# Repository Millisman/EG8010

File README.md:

# EG8010
Collection of designs for the EG8010 (ASIC for single-phase SPWM control H-bridge)

# EG8010_A0
EG8010_A0 is the inverter version to replace EGS002. Uses TLP250 optical isolated drivers and a Totem-pole current amplifier to drive high gate capacitance MOSFET transistors. A four-pin Kelvin circuit is used for all connections.

The connection diagram has a minimum of parts. An external +5V power supply is not required if the 7805 is populated on board. The fan is controlled directly from the printed circuit board. Twisted wires are indicated by ovals. Please don't separate them.

# MIT License
Design is distributed under the terms of the MIT license.

You can use this project for personal and business.
You can make it and sell it.
You may modify this project as you see fit.
You are bound by the copyright.

NO WARRANTIES of any kind are given!

All actions are at your OWN RISK!

Copyright (c) 2023, Sergey Kostyanoy <contact@arduino.uno>

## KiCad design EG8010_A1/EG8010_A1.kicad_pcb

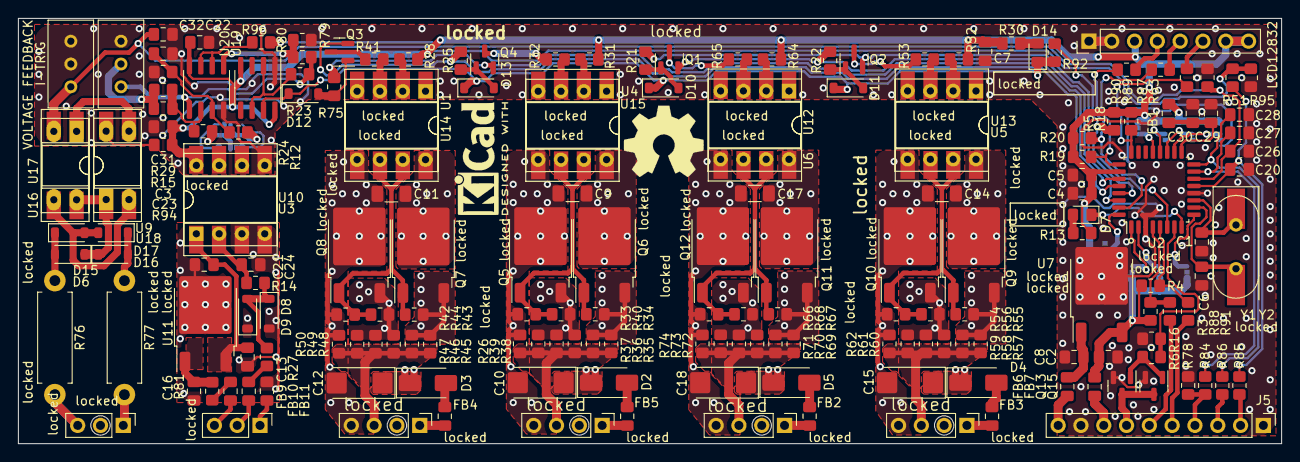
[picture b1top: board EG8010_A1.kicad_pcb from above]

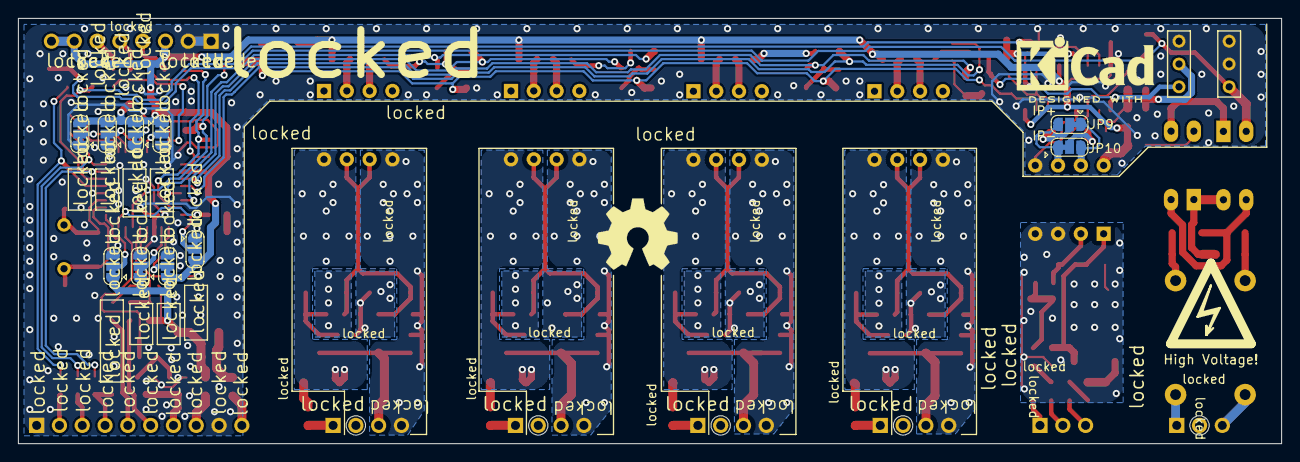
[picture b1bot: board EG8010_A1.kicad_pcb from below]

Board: 2 copper layers, 140.7 x 47.4 mm, 201 parts (13 on the bottom side), 123 nets.

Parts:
C1, C3, C6, C31: 22pF; C_0805_2012Metric_Pad1.18x1.45mm_HandSolder
C2, C4, C13, C16, C30, C32: 1uF; C_0805_2012Metric_Pad1.18x1.45mm_HandSolder
C5, C7, C8, C20, C21, C22, C23, C26, C27, C28, C29: 100nF; C_0805_2012Metric_Pad1.18x1.45mm_HandSolder
C9, C11, C14, C17: 10uF 50V; C_1206_3216Metric_Pad1.33x1.80mm_HandSolder
C10, C12, C15, C18: 10uF 35V; CP_EIA-6032-15_Kemet-U_Pad2.25x2.35mm_HandSolder
C24: 330pF; C_0805_2012Metric_Pad1.18x1.45mm_HandSolder
D2, D3, D4, D5: US1M; D_SMA
D6, D8, D9, D10, D11, D12, D13, D15, D16, D17: 1N4148W; D_SOD-123
D7: STATUS; LED_0805_2012Metric_Pad1.15x1.40mm_HandSolder
D14: OVC; LED_0805_2012Metric_Pad1.15x1.40mm_HandSolder
FB1, FB2, FB3, FB4, FB5, FB6, FB7, FB9, FB10, FB11: 600Ω@100MHz; C_0805_2012Metric_Pad1.18x1.45mm_HandSolder
HV1: High Voltage!; High_Voltage_Logo_10mm
J1, J2, J3, J4: C2.54_01x04_Pin; PinHeader_1x04_P2.54mm_Vertical
J5: Conn_01x10_Pin; PinHeader_1x10_P2.54mm_Vertical
J6: VOLTAGE; PinHeader_1x03_P2.54mm_Vertical
J7: CURRENT; PinHeader_1x03_P2.54mm_Vertical
JP1: FRQSEL1; SolderJumper-3_P1.3mm_Bridged12_RoundedPad1.0x1.5mm
JP2: FRQSEL0; SolderJumper-3_P1.3mm_Bridged12_RoundedPad1.0x1.5mm
JP3: DT0; SolderJumper-3_P1.3mm_Bridged12_RoundedPad1.0x1.5mm
JP4: DT1; SolderJumper-3_P1.3mm_Bridged12_RoundedPad1.0x1.5mm
JP5: VVVF; SolderJumper-3_P1.3mm_Bridged12_RoundedPad1.0x1.5mm
JP6: SST; SolderJumper-3_P1.3mm_Bridged12_RoundedPad1.0x1.5mm
JP7: MODSEL; SolderJumper-3_P1.3mm_Bridged12_RoundedPad1.0x1.5mm
JP8: SPWTYP; SolderJumper-3_P1.3mm_Bridged12_RoundedPad1.0x1.5mm
JP9: IP+; SolderJumper-3_P1.3mm_Bridged12_RoundedPad1.0x1.5mm
JP10: IP-; SolderJumper-3_P1.3mm_Bridged12_RoundedPad1.0x1.5mm
KICAD1: KiCad-Logo2_6mm_SilkScreen
KICAD2: KiCad-Logo2_5mm_SilkScreen
LCD12832: C2.54_01x08_Pin; PinHeader_1x08_P2.54mm_Vertical
OSHW1, OSHW2: Logo_Open_Hardware_Small; OSHW-Symbol_8.9x8mm_SilkScreen
Q1, Q2, Q3, Q4, Q13, Q15: 2N7002; SOT-23
Q5, Q8, Q10, Q12: PNP; TO-252-2
Q6, Q7, Q9, Q11: NPN; TO-252-2
R3, R4, R5, R12, R15, R16, R18, R19, R20, R24, R26, R29, R33, R42, R50, R51, R54, R62, R63, R66, R74, R78, R80, R84, R85, R86: 10K; R_0805_2012Metric_Pad1.20x1.40mm_HandSolder
R6, R13, R21, R22, R23, R25, R30, R75: 2.2K; R_0805_2012Metric_Pad1.20x1.40mm_HandSolder
R14, R27, R35, R36, R37, R38, R39, R45, R46, R47, R48, R49, R57, R58, R59, R60, R61, R69, R70, R71, R72, R73, R81: 4.7; R_0805_2012Metric_Pad1.20x1.40mm_HandSolder
R28, R31, R32, R34, R40, R41, R43, R44, R52, R53, R55, R56, R64, R65, R67, R68, R87, R88, R89, R90, R91, R92, R94: 470; R_0805_2012Metric_Pad1.20x1.40mm_HandSolder
R76, R77: 100K; R_Axial_DIN0411_L9.9mm_D3.6mm_P12.70mm_Horizontal
R79, R96: 10K**; R_0805_2012Metric_Pad1.20x1.40mm_HandSolder
R95: 68K; R_0805_2012Metric_Pad1.20x1.40mm_HandSolder
RV1, RV2: 25K; Potentiometer_Bourns_3296W_Vertical
U1, U4, U5, U6: TLP250; DIP-8_W8.89mm_SMDSocket_LongPads
U2: EG8010; LQFP-32_7x7mm_P0.8mm
U3: AMC1200; DIP-8_W8.89mm_SMDSocket_LongPads
U7, U11: 7805; TO-252-2
U9, U16: EL817; DIP-4_W8.89mm_SMDSocket_LongPads
U10: AMC1200; DIP-8_W7.62mm_Socket
U12, U13, U14, U15: TLP250; DIP-8_W7.62mm_Socket
U17, U18: EL817; DIP-4_W7.62mm_Socket_LongPads
U19: NE555D; SOIC-8_3.9x4.9mm_P1.27mm
U20: LM358; SOIC-8_3.9x4.9mm_P1.27mm
Y1: 12Mhz; Crystal_SMD_HC49-SD
Y2: 12Mhz; Crystal_HC49-4H_Vertical

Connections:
/DT0: JP3.2 (C), U2.2 (DT0)
/DT1: JP4.2 (C), U2.1 (DT1)
/ENABLE: D10.1 (K), D11.1 (K), D12.1 (K), D13.1 (K), D14.1 (K), R92.2, U19.7 (DIS)
/FANCTR: R6.1, R16.2, U2.7 (FANCTR)
/FRQSEL0: JP2.2 (C), U2.18 (FRQSEL0)
/FRQSEL1: JP1.2 (C), U2.19 (FRQSEL1)
/FRQVFB2: C28.1, R86.1, U2.16 (FRQADJ/VFB2)
/IFB: C26.1, R63.2, R96.1, U2.14 (IFB)
/LCDCLK: R18.2, R87.2, U2.24 (LCDCLK)
/LCDDI: R19.2, R89.2, U2.25 (LCDDI)
/LCDEN: R20.2, R90.2, U2.31 (LCDEN)
/LEDOUT: D7.1 (K), U2.8 (LEDOUT)
/MODSEL: JP7.2 (C), U2.20 (MODSEL)
/REF5V0: C29.1, C30.2, FB1.1, U2.17 (VREF)
/RXD: R3.1, R88.2, U2.4 (RXD)
/SPWMEN: R5.1, R92.1, U2.6 (SPWMEN)
/SPWTYP: JP8.2 (C), U2.9 (PWMTYP)
/SST: JP6.2 (C), U2.21 (SST)
/TFB: C27.1, R84.1, U2.15 (TFB)
/TXD: R4.1, R91.2, U2.5 (TXD)
/VCC5V0: C2.1, C4.1, C5.1, C7.2, C22.2, C23.1, FB1.2, FB7.2, JP1.3 (B), JP2.3 (B), JP3.1 (A), JP4.1 (A), JP5.3 (B), JP6.1 (A), JP7.3 (B), JP8.1 (A), LCD12832.3, LCD12832.7, LCD12832.8, R3.2, R4.2, R5.2, R13.2, R18.1, R19.1, R20.1, R28.1, R30.2, R31.1, R52.1, R64.1, R94.2, U2.26 (VCC), U3.8 (VDD2), U7.3 (VO), U10.8 (VDD2), U19.4 (R), U19.8 (VCC), U20.8 (V+)
/VFB: C20.1, R51.2, R85.1, U2.13 (VFB)
/VVVF: JP5.2 (C), U2.32 (VVVF)
GND: C1.1, C2.2, C4.2, C5.2, C6.1, C7.1, C8.2, C20.2, C22.1, C23.2, C26.2, C27.2, C28.2, C29.2, C30.1, C31.2, C32.2, J5.1, J5.9, JP1.1 (A), JP2.1 (A), JP3.3 (B), JP4.3 (B), JP5.1 (A), JP6.3 (B), JP7.1 (A), JP8.3 (B), LCD12832.1, LCD12832.2, Q13.2 (S), Q15.2 (S), R16.1, R29.2, R63.1, R78.1, R80.1, R95.2, RV1.3, RV2.2, RV2.3, U2.3 (GND), U2.12 (GND), U3.5 (GND2), U7.2 (GND), U10.5 (GND2), U19.1 (GND), U20.4 (V-)
unnamed: C3.2, R15.1, RV1.2
unnamed: C32.1, R51.1, R95.1, RV2.1, U16.2, U17.2
unnamed: D2.2 (A), FB5.2
unnamed: C9.2, C10.1, D2.1 (K), Q6.2 (C), U4.8 (VCC), U15.8 (VCC)
unnamed: D3.2 (A), FB4.2
unnamed: C11.2, C12.1, D3.1 (K), Q7.2 (C), U1.8 (VCC), U14.8 (VCC)
unnamed: D4.2 (A), FB3.2
unnamed: C14.2, C15.1, D4.1 (K), Q9.2 (C), U5.8 (VCC), U13.8 (VCC)
unnamed: D5.2 (A), FB2.2
unnamed: C17.2, C18.1, D5.1 (K), Q11.2 (C), U6.8 (VCC), U12.8 (VCC)
unnamed: D7.2 (A), R13.1
unnamed: C13.2, C16.2, C21.2, C24.2, D8.2 (A), D9.1 (K), FB11.1, U3.3 (IN-), U3.4 (GND1), U10.3 (IN-), U10.4 (GND1), U11.2 (GND)
unnamed: D8.1 (K), D9.2 (A), R14.1, R27.2
unnamed: D10.2 (A), Q1.1 (G), R21.2
unnamed: D11.2 (A), Q2.1 (G), R22.1
unnamed: D12.2 (A), Q3.1 (G), R75.2
unnamed: D13.2 (A), Q4.1 (G), R25.1
unnamed: D14.2 (A), R30.1
unnamed: D15.2 (A), D17.2 (A), U9.2, U16.3, U17.3, U18.2
unnamed: D6.2 (A), D15.1 (K), R76.2
unnamed: D16.2 (A), D17.1 (K), R77.2
unnamed: D6.1 (K), D16.1 (K), U9.1, U16.4, U17.4, U18.1
unnamed: FB9.1, R81.2
unnamed: FB10.1, R27.1
unnamed: FB5.1, J1.1
unnamed: J1.3, R26.2, R35.2, R36.2, R37.2, R38.2, R39.2
unnamed: C9.1, C10.2, J1.4, Q5.2 (C), R26.1, R33.1, U4.5 (VEE), U15.5 (VEE)
unnamed: FB4.1, J2.1
unnamed: J2.3, R45.2, R46.2, R47.2, R48.2, R49.2, R50.2
unnamed: C11.1, C12.2, J2.4, Q8.2 (C), R42.1, R50.1, U1.5 (VEE), U14.5 (VEE)
unnamed: FB3.1, J3.1
unnamed: J3.3, R57.2, R58.2, R59.2, R60.2, R61.2, R62.2
unnamed: C14.1, C15.2, J3.4, Q10.2 (C), R54.1, R62.1, U5.5 (VEE), U13.5 (VEE)
unnamed: FB2.1, J4.1
unnamed: J4.3, R69.2, R70.2, R71.2, R72.2, R73.2, R74.2
unnamed: C17.1, C18.2, J4.4, Q12.2 (C), R66.1, R74.1, U6.5 (VEE), U12.5 (VEE)
unnamed: J5.2, R85.2
unnamed: J5.3, R86.2
unnamed: J5.4, R78.2, R84.2
unnamed: J5.5, R91.1
unnamed: J5.6, R88.1
unnamed: J5.7, Q13.3 (D), Q15.3 (D)
unnamed: FB7.1, J5.8
unnamed: FB6.1, J5.10
unnamed: J6.1, R77.1
unnamed: J6.3, R76.1
unnamed: FB11.2, J7.1
unnamed: FB10.2, J7.2
unnamed: FB9.2, J7.3
unnamed: JP9.2 (C), R12.2
unnamed: JP9.3 (B), JP10.1 (A), U3.6 (OUT-), U10.6 (OUT-)
unnamed: JP9.1 (A), JP10.3 (B), U3.7 (OUT+), U10.7 (OUT+)
unnamed: JP10.2 (C), R24.2
unnamed: LCD12832.4, R90.1
unnamed: LCD12832.5, R89.1
unnamed: LCD12832.6, R87.1
unnamed: Q1.3 (D), R65.1
unnamed: Q1.2 (S), R22.2, U2.30 (SPWMOUT4)
unnamed: Q2.3 (D), R53.1
unnamed: Q2.2 (S), R21.1, U2.29 (SPWMOUT3)
unnamed: Q3.3 (D), R41.1
unnamed: Q3.2 (S), R25.2, U2.28 (SPWMOUT2)
unnamed: Q4.3 (D), R32.1
unnamed: Q4.2 (S), R75.1, U2.27 (SPWMOUT1)
unnamed: Q5.1 (B), Q6.1 (B), R33.2, R34.1, R40.1, U4.6 (VO), U4.7 (VO), U15.6 (VO), U15.7 (VO)
unnamed: Q5.3 (E), R37.1, R38.1, R39.1, R40.2
unnamed: Q6.3 (E), R34.2, R35.1, R36.1
unnamed: Q7.1 (B), Q8.1 (B), R42.2, R43.1, R44.1, U1.6 (VO), U1.7 (VO), U14.6 (VO), U14.7 (VO)
unnamed: Q7.3 (E), R43.2, R45.1, R46.1
unnamed: Q8.3 (E), R44.2, R47.1, R48.1, R49.1
unnamed: Q9.3 (E), R55.2, R57.1, R58.1
unnamed: Q9.1 (B), Q10.1 (B), R54.2, R55.1, R56.1, U5.6 (VO), U5.7 (VO), U13.6 (VO), U13.7 (VO)
unnamed: Q10.3 (E), R56.2, R59.1, R60.1, R61.1
unnamed: Q11.1 (B), Q12.1 (B), R66.2, R67.1, R68.1, U6.6 (VO), U6.7 (VO), U12.6 (VO), U12.7 (VO)
unnamed: Q11.3 (E), R67.2, R69.1, R70.1
unnamed: Q12.3 (E), R68.2, R71.1, R72.1, R73.1
unnamed: Q13.1 (G), Q15.1 (G), R6.2
unnamed: R23.1, R79.2, RV1.1, U20.1
unnamed: R94.1, U9.4, U18.4
unnamed: R28.2, U1.2 (A), U14.2 (A)
unnamed: R41.2, U1.3 (C), U14.3 (C)
unnamed: C6.2, U2.10 (OSC1), Y1.2, Y2.2
unnamed: C1.2, U2.11 (OSC2), Y1.1, Y2.1
unnamed: C8.1, FB6.2, U7.1 (VI)
unnamed: C24.1, R14.2, U3.2 (IN+), U10.2 (IN+)
unnamed: C13.1, C21.1, U3.1 (VDD1), U10.1 (VDD1), U11.3 (VO)
unnamed: C16.1, R81.1, U11.1 (VI)
unnamed: R64.2, U6.2 (A), U12.2 (A)
unnamed: R65.2, U6.3 (C), U12.3 (C)
unnamed: R52.2, U5.2 (A), U13.2 (A)
unnamed: R53.2, U5.3 (C), U13.3 (C)
unnamed: R31.2, U4.2 (A), U15.2 (A)
unnamed: R32.2, U4.3 (C), U15.3 (C)
unnamed: U9.3, U16.1, U17.1, U18.3
unnamed: R23.2, U19.2 (TR), U19.6 (THR)
unnamed: C31.1, R12.1, R29.1, U20.3 (+)
unnamed: C3.1, R15.2, R24.1, U20.2 (-)
unnamed: R79.1, R80.2, U20.5 (+)
unnamed: R96.2, U20.6 (-), U20.7

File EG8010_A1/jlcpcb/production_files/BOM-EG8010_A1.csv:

Comment,Designator,Footprint,LCSC
EL817,"U16,U9",DIP-4_W8.89mm_SMDSocket_LongPads,C106900
NPN,"Q11,Q6,Q7,Q9",TO-252-2,C138779
PNP,"Q10,Q12,Q5,Q8",TO-252-2,C138783
10K,"R12,R15,R16,R18,R19,R20,R24,R26,R29,R3,R33,R4,R42,R5,R50,R51,R54,R62,R63,R66,R74,R78,R79,R80,R84,R85,R86,R96",R_0805_2012Metric_Pad1.20x1.40mm_HandSolder,C17414
2.2K,"R13,R21,R22,R23,R25,R30,R6,R75",R_0805_2012Metric_Pad1.20x1.40mm_HandSolder,C17520
4.7,"R14,R27,R35,R36,R37,R38,R39,R45,R46,R47,R48,R49,R57,R58,R59,R60,R61,R69,R70,R71,R72,R73,R81",R_0805_2012Metric_Pad1.20x1.40mm_HandSolder,C17675
470,"R28,R31,R32,R34,R40,R41,R43,R44,R52,R53,R55,R56,R64,R65,R67,R68,R87,R88,R89,R90,R91,R92,R94",R_0805_2012Metric_Pad1.20x1.40mm_HandSolder,C17710
68K,R95,R_0805_2012Metric_Pad1.20x1.40mm_HandSolder,C17801
22pF,"C1,C3,C31,C6",C_0805_2012Metric_Pad1.18x1.45mm_HandSolder,C1804
EL817,"U17,U18",DIP-4_W7.62mm_Socket_LongPads,C181890
TLP250,"U1,U4,U5,U6",DIP-8_W8.89mm_SMDSocket_LongPads,C2802426
100nF,"C20,C21,C22,C23,C24,C26,C27,C28,C29,C5,C7,C8",C_0805_2012Metric_Pad1.18x1.45mm_HandSolder,C28233
1uF,"C13,C16,C2,C30,C32,C4",C_0805_2012Metric_Pad1.18x1.45mm_HandSolder,C28323
 600Ω@100MHz,"FB1,FB10,FB11,FB2,FB3,FB4,FB5,FB6,FB7,FB9",C_0805_2012Metric_Pad1.18x1.45mm_HandSolder,C2858468
10uF 50V,"C11,C14,C17,C9",C_1206_3216Metric_Pad1.33x1.80mm_HandSolder,C303950
AMC1200,U3,DIP-8_W8.89mm_SMDSocket_LongPads,C39673
TLP250,"U12,U13,U14,U15",DIP-8_W7.62mm_Socket,C4078
US1M,"D2,D3,D4,D5",D_SMA,C412437
10uF 35V,"C10,C12,C15,C18",CP_EIA-6032-15_Kemet-U_Pad2.25x2.35mm_HandSolder,C435847
25K,"RV1,RV2",Potentiometer_Bourns_3296W_Vertical,C55264
7805,"U11,U7",TO-252-2,C58069
12Mhz,Y1,Crystal_SMD_HC49-SD,C6555079
100K,"R76,R77",R_Axial_DIN0411_L9.9mm_D3.6mm_P12.70mm_Horizontal,C714116
NE555D,U19,SOIC-8_3.9x4.9mm_P1.27mm,C7593
LM358,U20,SOIC-8_3.9x4.9mm_P1.27mm,C7950
1N4148W,"D10,D11,D12,D13,D15,D16,D17,D6,D8,D9",D_SOD-123,C81598
EG8010,U2,LQFP-32_7x7mm_P0.8mm,C81683
OVC,"D14,D7",LED_0805_2012Metric_Pad1.15x1.40mm_HandSolder,C84256
2N7002,"Q1,Q13,Q15,Q2,Q3,Q4",SOT-23,C8545
VOLTAGE,J6,PinHeader_1x03_P2.54mm_Vertical,
Conn_01x10_Pin,J5,PinHeader_1x10_P2.54mm_Vertical,
CURRENT,J7,PinHeader_1x03_P2.54mm_Vertical,
AMC1200,U10,DIP-8_W7.62mm_Socket,
High Voltage!,HV1,High_Voltage_Logo_10mm,

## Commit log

2023-10-14 Add files via upload
    4 wire kelvin connection VS standard EGS002
2023-10-23 Added rev A1 (SPWM ISO)

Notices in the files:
EG8010_A1/EG8010_A1.kicad_pcb:
THIS DESIGN IS PROVIDED \"AS IS\", WITHOUT WARRANTY OF ANY KIND - MIT License
licensed under MIT
